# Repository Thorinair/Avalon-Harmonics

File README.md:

# Avalon Harmonics

This repository provides a collection of modular synthesizer modules designed by Thorinair under the brand name "Avalon Harmonics". The modules are all designed to have some associations with the [Avali](https://avali.fandom.com/wiki/The_Official_Avali_Wiki) fictional species and to have some unique functionalities - mostly stuff that I needed but couldn't readily find elsewhere.

* **Official Website:** [avalon-harmonics.com](https://avalon-harmonics.com/)
* **Official Twitter:** [@AvalonHarmonics](https://twitter.com/AvalonHarmonics)
* **Official Instagram:** [avalonharmonics](https://www.instagram.com/avalonharmonics/)

## Licensing

All hardware designs are licensed under the [cc-by-sa-4.0](https://creativecommons.org/licenses/by-sa/4.0/legalcode) license.

If designing a derivative module based on one of Avalon Harmonics modules, do not use the name "Avalon Harmonics". Additionally, you should not call the derivative module as one of the original Avalon Harmonics modules.

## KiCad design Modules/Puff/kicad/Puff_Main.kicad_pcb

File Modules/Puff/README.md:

# Avalon Harmonics Puff

**Stereo multimode filter with Ping input**

Puff is a stereo multimode filter with a state variable circuit. The filter provides separate Low Pass, Band Pass and High Pass outputs for both channels, has an attenuvertable CV input, a V/OCT input, and a dedicated Ping input. The circuit has some interesting quirks in its design, resulting in some very gritty sounds in higher resonance levels. Note that the filter can't continuously self-oscillate. **Features a golden (ENIG coated) panel.**

The filter has two audio inputs for a left and right channel. For convenience, right channel is normalled to the left channel when nothing is plugged into it. Both left and right channels have separate LP, BP and HP outputs, allowing all three of the filter types to be used at the same time.

Filter circuit is based on Thomas Henry's VCF circuit, with some modifications and adjustments. Cutoff can be controlled with the CUT knob, and resonance with the RES knob. CUT knob's effective range is from around 9 o'clock to 3 o'clock, with the extra range being useful when combined with a CV signal for more aggressive cutoffs etc. Signal fed into the CV input jack can be attenuverted with the ATN knob, allowing for inverting of an envelope signal, an LFO, or whatever is plugged in. Cutoff can also be controlled with a 1V/OCT signal through the V/OCT jack. Frequency of the cutoff can be tuned, and the tuning trimmer is exposed on the front panel where the tuning fork icon is, just to the bottom-left of the CUT knob. A screwdriver can be used to adjust it.

Resonance on this filter is interesting, as it gets progressively more unstable in higher ranges. Above around 3 o'clock of the RES knob, standing wave-like peaks start appearing in certain frequencies of the cutoff, which correspond to the frequency of the signal fed into the filter. These peaks can get quite loud on high resonance levels, so this whole section of the knob is marked with a warning symbol. An IN GAIN knob is provided, which can be used to lower the input signal's level. A quieter input signal will result in quieter resonance peaks, allowing the peaks to be tamed to a managable level.

Lastly, the filter has a dedicated PING input jack. A gate, trigger, or even an LFO can be plugged into this jack to ping the filter. The circuit simply converts an incoming signal so that, above a certain threshold, it causes a short DC offset, effectively plucking the filter's resonance. Ping only really works in high resonance levels, so I suggest maxing out the RES knob for this application. One way to use it is to connect a V/OCT signal, as well as a gate signal of a sequencer, and directly play notes on the filter. LP, BP and HP outputs will all have a slightly different sound when being pinged, so there is a lot to explore! An LED next to the PING jack flashes on each ping.

**CALIBRATION:** V/OCT of the cutoff can be calibrated. All modules I build and ship come pre-calibrated, but there might be a slight difference depending on your power supply or some other factors like temperature. To calibrate Puff, set the RES knob to the max, keep the audio inputs unplugged, connect your keyboard or sequencer's V/OCT and GATE to Puff's V/OCT and PING, and start playing notes. I suggest using a proper tuner, some modules can do this, and there is also Korg's ST1K tuner. Calibration of Puff is very similar to any VCO, but you need to constantly send it gates or triggers to keep the tone going, as it can't continuously self-oscillate.

*How did the name "Puff" happen? I wanted a cute, silly and unique name. I played around in my head with multiple different ones like Fluff, Floof, Poof, Puff, but eventually ended up with Puff. Puff as in, a pufferfish, a puffed up bird, etc!*

Visit Website: https://avalon-harmonics.com/module/Puff/

### Features

* Stereo multimode filter
* Separate LP, BP and HP outputs
* Attenuvertable CV input
* Tunable V/OCT input
* Dedicated Ping input
* Fully analog circuitry
* Wrong polarity protection
* Skiff friendly
* Size: 8HP
* Depth: 25mm
* Power: +12V: 35mA, -12V: 35mA

### Credits

* Filter circuit based on [Thomas Henry's VCF circuit](https://www.birthofasynth.com/Thomas_Henry/Pages/VCF-1.html)
* Tuning Fork Icon created by [Freepik - Flaticon](https://www.flaticon.com/free-icons/vibration)
* Alert Icon created by [Freepik - Flaticon](https://www.flaticon.com/free-icons/alert)

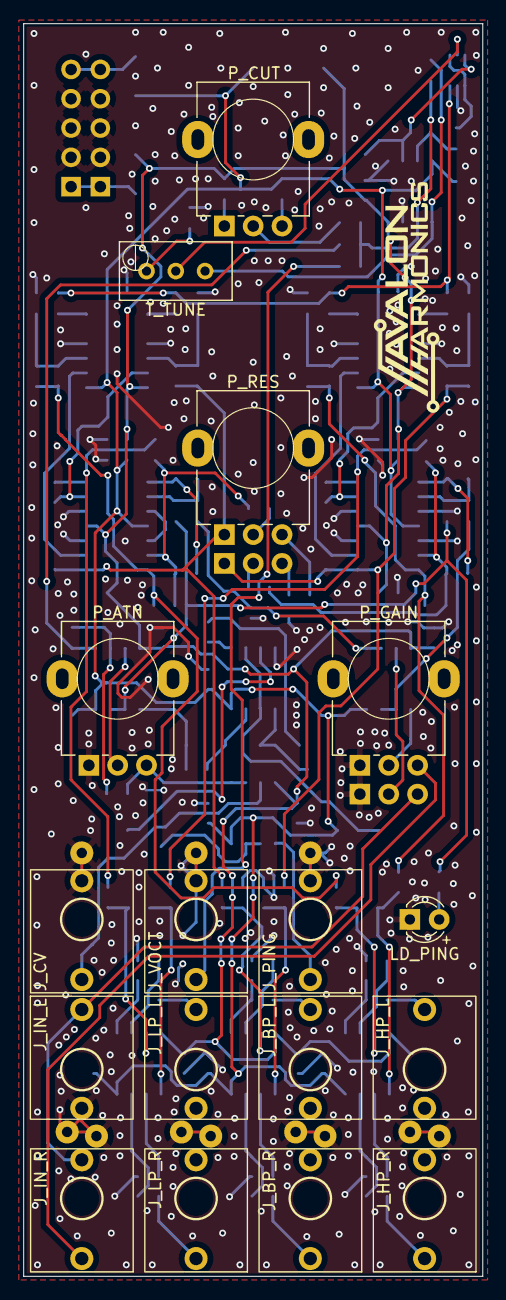
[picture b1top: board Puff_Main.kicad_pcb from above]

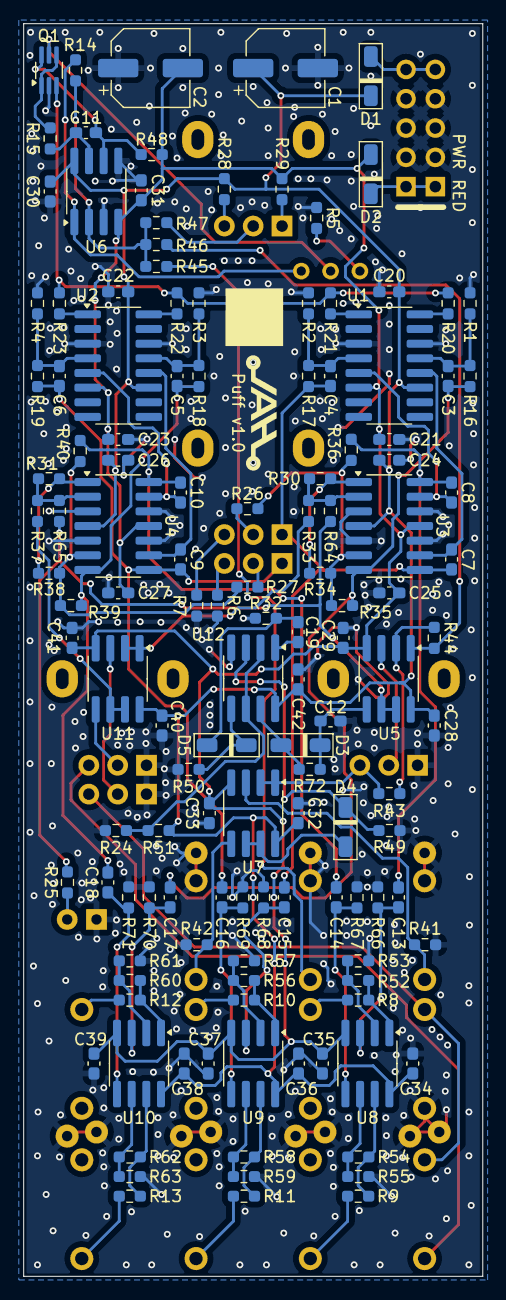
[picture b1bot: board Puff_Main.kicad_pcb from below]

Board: 2 copper layers, 39.8 x 108.6 mm, 150 parts (133 on the bottom side), 91 nets.

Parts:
C1, C2: 47uF; CP_Elec_6.3x5.3
C3, C4, C5, C6: 10pF; C_0603_1608Metric_Pad1.08x0.95mm_HandSolder
C7, C8, C9, C10: 330pF; C_0603_1608Metric_Pad1.08x0.95mm_HandSolder
C11: 1nF; C_0603_1608Metric_Pad1.08x0.95mm_HandSolder
C12: 47nF; C_0603_1608Metric_Pad1.08x0.95mm_HandSolder
C13, C14, C15, C16, C17, C18, C19, C20, C21, C22, C23, C24, C25, C26, C27, C28, C29, C30, C31, C32, C33, C34, C35, C36, C37, C38, C39, C40, C41, C42: 0.1uF; C_0603_1608Metric_Pad1.08x0.95mm_HandSolder
D1, D2: FM4001; D_SOD-123F_AH
D3, D4, D5: 1N4148W; D_SOD-123F_AH
J_BP_L: PJ301M-12; PJ301M-12 Offset
J_BP_R: PJ301M-12; PJ301M-12 Offset
J_CV: PJ301M-12
J_HP_L: PJ301M-12; PJ301M-12 Offset
J_HP_R: PJ301M-12; PJ301M-12 Offset
J_IN_L: PJ301M-12; PJ301M-12 Offset
J_IN_R: PJ301M-12; PJ301M-12 Offset
J_LP_L: PJ301M-12; PJ301M-12 Offset
J_LP_R: PJ301M-12; PJ301M-12 Offset
J_PING: PJ301M-12
J_VOCT: PJ301M-12
LD_PING: LED; LED_D3.0mm_FlatTop
PWR1: PWR_10_Pin; Eurorack Power 10 Pin
P_ATN: B50k; Potentiometer Alpha RD901F-40-00D
P_CUT: B100k; Potentiometer Alpha RD901F-40-00D
P_GAIN: A100k; Potentiometer Alpha Dual RD901F-40-00D
P_RES: B50k; Potentiometer Alpha Dual RD901F-40-00D
Q1: BCM857BS; SOT-363_SC-70-6_Handsoldering
R1, R2, R3, R4: 22; R_0603_1608Metric_Pad0.98x0.95mm_HandSolder
R5: 390; R_0603_1608Metric_Pad0.98x0.95mm_HandSolder
R6, R7: 220; R_0603_1608Metric_Pad0.98x0.95mm_HandSolder
R8, R9, R10, R11, R12, R13: 1k; R_0603_1608Metric_Pad0.98x0.95mm_HandSolder
R14: 2k; R_0603_1608Metric_Pad0.98x0.95mm_HandSolder
R15: 5.6k; R_0603_1608Metric_Pad0.98x0.95mm_HandSolder
R16, R17, R18, R19: 11k; R_0603_1608Metric_Pad0.98x0.95mm_HandSolder
R20, R21, R22, R23, R28, R29: 15k; R_0603_1608Metric_Pad0.98x0.95mm_HandSolder
R24, R25: 22k; R_0603_1608Metric_Pad0.98x0.95mm_HandSolder
R26, R27: 27k; R_0603_1608Metric_Pad0.98x0.95mm_HandSolder
R30, R31, R32: 47k; R_0603_1608Metric_Pad0.98x0.95mm_HandSolder
R33, R34, R35, R36, R37, R38, R39, R40, R41, R42, R43, R44, R45, R46, R47, R48, R49, R50, R51, R52, R53, R54, R55, R56, R57, R58, R59, R60, R61, R62, R63: 100k; R_0603_1608Metric_Pad0.98x0.95mm_HandSolder
R64, R65: 200k; R_0603_1608Metric_Pad0.98x0.95mm_HandSolder
R66, R67, R68, R69, R70, R71: 240k; R_0603_1608Metric_Pad0.98x0.95mm_HandSolder
R72: 1M; R_0603_1608Metric_Pad0.98x0.95mm_HandSolder
T_TUNE: B100; Potentiometer_Bourns_3296W_Vertical
U1, U2: LM13700; SO-16_3.9x9.9mm_P1.27mm_AH
U3, U4: TL074; SO-14_3.9x8.65mm_P1.27mm_AH
U5, U6, U7, U8, U9, U10, U11, U12: TL072; SO-8_3.9x4.9mm_P1.27mm_AH

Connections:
+12V: C1.1, C20.1, C22.1, C24.1, C26.1, C28.1, C30.1, C32.1, C34.1, C36.1, C38.1, C40.1, C42.1, D1.1 (K), R28.2, R51.2, U1.11 (V+), U2.11 (V+), U3.4 (V+), U4.4 (V+), U5.8 (V+), U6.8 (V+), U7.8 (V+), U8.8 (V+), U9.8 (V+), U10.8 (V+), U11.8 (V+), U12.8 (V+)
-12V: C2.2, C21.2, C23.2, C25.2, C27.2, C29.2, C31.2, C33.2, C35.2, C37.2, C39.2, C41.2, D2.2 (A), R29.1, R48.1, U1.6 (V-), U2.6 (V-), U3.11 (V-), U4.11 (V-), U5.4 (V-), U6.4 (V-), U7.4 (V-), U8.4 (V-), U9.4 (V-), U10.4 (V-), U11.4 (V-)
/ATN: P_ATN.3, R43.2, U7.1, U7.2 (-)
/BP_L: C4.1, C7.2, C15.1, P_RES.1, R17.2, U3.8
/BP_R: C6.1, C9.2, C16.1, P_RES.4, R19.2, U4.8
/CTRL: Q1.3 (C2), R20.1, R21.1, R22.1, R23.1
/DIV: R24.1, R51.1, U12.2 (-), U12.6 (-)
/HP_L: C3.1, C17.1, R16.2, R35.1, U3.7
/HP_R: C5.1, C18.1, R18.2, R39.1, U4.7
/IN_L: R33.2, U11.1, U11.2 (-)
/IN_PING: D4.2 (A), U7.6 (-), U7.7
/IN_R: R37.2, U11.6 (-), U11.7
/LP_L: C8.2, C13.1, R36.1, U3.14
/LP_R: C10.2, C14.1, R40.1, U4.14
/PING: R25.2, R64.2, R65.2, U5.6 (-), U5.7
/RES_L_2: P_RES.2, R26.2
/RES_R_2: P_RES.5, R27.2
/VOCT: J_VOCT.SIG, R45.2
GND: C1.2, C2.1, C12.2, C20.2, C21.1, C22.2, C23.1, C24.2, C25.1, C26.2, C27.1, C28.2, C29.1, C30.2, C31.1, C32.2, C33.1, C34.2, C35.1, C36.2, C37.1, C38.2, C39.1, C40.2, C41.1, C42.2, J_BP_L.GND, J_BP_R.GND, J_CV.GND, J_CV.SW, J_HP_L.GND, J_HP_R.GND, J_IN_L.GND, J_IN_L.SW, J_IN_R.GND, J_LP_L.GND, J_LP_R.GND, J_PING.GND, J_PING.SW, J_VOCT.GND, J_VOCT.SW, LD_PING.1 (K), PWR1.2 (GND), P_ATN.1, P_GAIN.1, P_GAIN.4, Q1.2 (B1), R1.1, R2.1, R3.1, R4.1, R5.1, R6.1, R7.1, R24.2, R32.2, R41.1, R42.1, R49.1, R50.1, R53.1, R55.1, R57.1, R59.1, R61.1, R63.1, R66.1, R67.1, R68.1, R69.1, R70.1, R71.1, U1.3 (+), U1.14 (+), U2.3 (+), U2.14 (+), U3.3 (+), U3.5 (+), U3.10 (+), U3.12 (+), U4.3 (+), U4.5 (+), U4.10 (+), U4.12 (+), U6.3 (+), U6.5 (+), U12.4 (V-)
unnamed: C11.2, R15.1, U6.7
unnamed: C19.1, U12.1
unnamed: D1.2 (A), PWR1.1 (+12V)
unnamed: D2.1 (K), PWR1.3 (-12V)
unnamed: D3.2 (A), R72.2, U12.7
unnamed: C12.1, D3.1 (K), R72.1, U5.5 (+)
unnamed: D4.1 (K), R49.2, U12.3 (+)
unnamed: C19.2, D5.2 (A), R32.1
unnamed: D5.1 (K), R50.2, U12.5 (+)
unnamed: J_BP_L.SIG, R10.1
unnamed: J_BP_R.SIG, R11.1
unnamed: J_HP_L.SIG, R12.1
unnamed: J_HP_R.SIG, R13.1
unnamed: J_IN_L.SIG, J_IN_R.SW, P_GAIN.6
unnamed: J_IN_R.SIG, P_GAIN.3
unnamed: J_LP_L.SIG, R8.1
unnamed: J_LP_R.SIG, R9.1
unnamed: LD_PING.2 (A), R25.1
unnamed: P_CUT.1, R29.2
unnamed: P_CUT.2, R47.2
unnamed: P_CUT.3, R28.1
unnamed: P_RES.3, R7.2
unnamed: P_RES.6, R6.2
unnamed: C11.1, Q1.6 (C1), R48.2, U6.6 (-)
unnamed: Q1.1 (E1), Q1.4 (E2), R15.2
unnamed: Q1.5 (B2), T_TUNE.2
unnamed: R5.2, T_TUNE.1
unnamed: R10.2, R56.1, U9.1
unnamed: R11.2, R58.1, U9.7
unnamed: R12.2, R60.1, U10.1
unnamed: R13.2, R62.1, U10.7
unnamed: R14.1, T_TUNE.3, U6.1
unnamed: R20.2, U1.16
unnamed: R21.2, U1.1
unnamed: R22.2, U2.16
unnamed: R23.2, U2.1
unnamed: R30.1, R34.2, U3.1
unnamed: R31.1, R38.2, U4.1
unnamed: R44.1, R46.2, U5.1
unnamed: R8.2, R52.1, U8.1
unnamed: R9.2, R54.1, U8.7
unnamed: C3.2, R1.2, R16.1, U1.13 (-)
unnamed: C4.2, R2.2, R17.1, U1.4 (-)
unnamed: C5.2, R3.2, R18.1, U2.13 (-)
unnamed: C6.2, R4.2, R19.1, U2.4 (-)
unnamed: R30.2, R33.1, R64.1, U3.2 (-)
unnamed: R26.1, R34.1, R35.2, R36.2, U3.6 (-)
unnamed: C7.1, U1.12, U3.9 (-)
unnamed: C8.1, U1.5, U3.13 (-)
unnamed: R31.2, R37.1, R65.1, U4.2 (-)
unnamed: R27.1, R38.1, R39.2, R40.2, U4.6 (-)
unnamed: C9.1, U2.12, U4.9 (-)
unnamed: C10.1, U2.5, U4.13 (-)
unnamed: P_ATN.2, U5.3 (+)
unnamed: R43.1, R44.2, U5.2 (-)
unnamed: R14.2, R45.1, R46.1, R47.1, U6.2 (-)
unnamed: J_CV.SIG, R41.2, U7.3 (+)
unnamed: J_PING.SIG, R42.2, U7.5 (+)
unnamed: C13.2, R66.2, U8.3 (+)
unnamed: R52.2, R53.2, U8.2 (-)
unnamed: C14.2, R67.2, U8.5 (+)
unnamed: R54.2, R55.2, U8.6 (-)
unnamed: C15.2, R68.2, U9.3 (+)
unnamed: R56.2, R57.2, U9.2 (-)
unnamed: C16.2, R69.2, U9.5 (+)
unnamed: R58.2, R59.2, U9.6 (-)
unnamed: C17.2, R70.2, U10.3 (+)
unnamed: R60.2, R61.2, U10.2 (-)
unnamed: C18.2, R71.2, U10.5 (+)
unnamed: R62.2, R63.2, U10.6 (-)
unnamed: P_GAIN.5, U11.3 (+)
unnamed: P_GAIN.2, U11.5 (+)

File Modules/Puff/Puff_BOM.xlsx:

Avalon Harmonics Puff
Qty | Value | Package | Ref | Description | Link |  |  |  | Alt Link
8 | 22 | R-0603 | R1-R8 | Resistor SMD | https://www.tme.eu/de/en/details/smd0603-22r-1%25/smd-resist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
2 | 220 | R-0603 | R6, R7 | Resistor SMD | https://www.tme.eu/de/en/details/smd0603-220r-1%25/smd-resis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
1 | 390 | R-0603 | R5 | Resistor SMD | https://www.tme.eu/de/en/details/smd0603-390r-1%25/smd-resis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
6 | 1k | R-0603 | R8-R13 | Resistor SMD | https://www.tme.eu/de/en/details/smd0603-1k-1%25/smd-resisto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
1 | 2k | R-0603 | R14 | Resistor SMD | https://www.tme.eu/de/en/details/smd0603-2k-1%25/smd-resisto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
1 | 5.6k | R-0603 | R15 | Resistor SMD | https://www.tme.eu/de/en/details/smd0603-5k6-1%25/smd-resist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
4 | 11k | R-0603 | R16-R19 | Resistor SMD | https://www.tme.eu/de/en/details/smd0603-11k-1%25/smd-resist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
6 | 15k | R-0603 | R20-R23, R28, R29 | Resistor SMD | https://www.tme.eu/de/en/details/smd0603-15k-1%25/smd-resist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
2 | 22k | R-0603 | R24, R25 | Resistor SMD | https://www.tme.eu/de/en/details/smd0603-22k-1%25/smd-resist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
2 | 27k | R-0603 | R26, R27 | Resistor SMD | https://www.tme.eu/de/en/details/smd0603-27k-1%25/smd-resist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
3 | 47k | R-0603 | R30-R32 | Resistor SMD | https://www.tme.eu/de/en/details/smd0603-47k-1%25/smd-resist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
31 | 100k | R-0603 | R33-R63 | Resistor SMD | https://www.tme.eu/de/en/details/smd0603-100k-1%25/smd-resis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
2 | 200k | R-0603 | R64, R65 | Resistor SMD | https://www.tme.eu/de/en/details/smd0603-200k-1%25/smd-resis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
6 | 240k | R-0603 | R66-R71 | Resistor SMD | https://www.tme.eu/de/en/details/crcw0603240kfktabc/smd-resi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
1 | 1M | R-0603 | R72 | Resistor SMD | https://www.tme.eu/de/en/details/cq0603-1m-1%25/smd-resistor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
1 | B100 | 3296W | T_TUNE | Multiturn Trimmer THT | https://www.thonk.co.uk/shop/25-turn-trimmer-potentiometer/
4 | 10pF | C-0603 | C3-C6 | Ceramic Capacitor SMD | https://www.tme.eu/de/en/details/0603n100k500ct/mlcc-smd-cap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
4 | 330pF | C-0603 | C7-C10 | Ceramic Capacitor SMD | https://www.tme.eu/de/en/details/0603b331k500ct/mlcc-smd-cap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
1 | 1nF | C-0603 | C11 | Ceramic Capacitor SMD | https://www.tme.eu/de/en/details/cl10b102kb8wpnc/mlcc-smd-ca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
1 | 47nF | C-0603 | C12 | Ceramic Capacitor SMD | https://www.tme.eu/de/en/details/cl10b473kb8nnnc/mlcc-smd-ca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
30 | 0.1uF | C-0603 | C13-C42 | Ceramic Capacitor SMD | https://www.tme.eu/de/en/details/0603b104k500ct/mlcc-smd-cap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
2 | 47uF | E-6.3x5.3mm | C1, C2 | Electrolytic Capacitor SMD | https://www.tme.eu/de/en/details/sc1e476m6l005vr/smd-electro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
2 | FM4001 | SOD123F | D1, D2 | Rectifier Diode SMD | https://www.tme.eu/de/en/details/fm4001-lge/smd-universal-di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
3 | 1N4148W | SOD123F | D3-D5 | Switching Diode SMD | https://www.tme.eu/de/en/details/1n4148w-dio/smd-universal-d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
1 | BCM857BS | SOT-363 | Q1 | PNP Dual Package SMD | https://www.tme.eu/de/en/details/bcm857bs.115/pnp-smd-transi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
2 | LM13700 | SO16 | U1, U2 | Dual OTA SMD | https://www.tme.eu/de/en/details/lm13700mx_nopb/smd-operatio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
2 | TL074 | SO14 | U3, U4 | Quad Op Amp SMD | https://www.tme.eu/de/en/details/tl074bcdt/smd-operational-a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
8 | TL072 | SO8 | U5-U12 | Dual Op Amp SMD | https://www.tme.eu/de/en/details/tl072cdr/smd-operational-am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
1 | B50k | Pot 9mm Alpha D-Shaft CENTRE DETENT* | P_ATN | Potentiometer Metal | https://www.thonk.co.uk/shop/alpha-9mm-pots-dshaft/
1 | A100k | Pot 9mm Alpha D-Shaft DUAL GANG* | P_GAIN | Potentiometer Metal | https://www.thonk.co.uk/shop/alpha-d-shaft-dual-gang/
1 | B50k | Pot 9mm Alpha D-Shaft DUAL GANG | P_RES | Potentiometer Metal | https://www.thonk.co.uk/shop/alpha-d-shaft-dual-gang/
1 | B100k | Pot 9mm Alpha D-Shaft | P_CUT | Potentiometer Metal | https://www.thonk.co.uk/shop/alpha-9mm-pots-dshaft/
1 | OSO5PA3HE4B | LED 3mm Flat | LD_PING | LED Orange | https://www.tme.eu/de/en/details/oso5pa3he4b/tht-leds-3mm/op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
11 | Thonkiconn | PJ398SM | J_CV, J_VOCT, J_PING, J_IN_L, J_IN_R, J_LP_L, J_LP_R, J_BP_L, J_BP_R, J_HP_L, J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 | Audio Jack | https://www.thonk.co.uk/shop/thonkiconn/
1 | 2x5 | Male Header 2.54mm | PWR | Header Connector | https://www.tme.eu/de/en/details/zl202-10g/pin-headers/connf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
4 | Black | Pushernut |  | Jack Nut | https://pushermanproductions.com/products/pushernuts-round-m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
6 | Gold | Pushernut |  | Jack Nut | https://pushermanproductions.com/products/pushernuts-round-m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
1 | Red | Pushernut |  | Jack Nut | https://pushermanproductions.com/products/pushernuts-round-m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
4 | Black | Alpha 9mm Nut |  | Potentiometer Nut | https://www.thonk.co.uk/shop/black-nuts-washers/
2 | Black D-Shaft Line | Bastl Style Alu Knob 10mm |  | Potentiometer Knob | https://www.thonk.co.uk/shop/bastl-knobs/
2 | Black D-Shaft Line | Bastl Style Alu Knob 15mm |  | Potentiometer Knob | https://www.thonk.co.uk/shop/bastl-knobs/
 | Parts with underline are on the front side of the PCB!
 | * Do not use the included washer. Tighten very gently so the PCB doesn't get sc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

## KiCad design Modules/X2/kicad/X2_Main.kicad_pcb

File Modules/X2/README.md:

# Avalon Harmonics X2

**4 channel voltage doubler**

X2 is a simple and compact module which will double the voltage level of any signal. Designed to be a perfect companion for the Avalon Harmonics CVMod8 V2 and CVMod4. **Features a golden (ENIG coated) panel.**

Some modules expect a higher voltage than 5V to trigger. This is where this module comes to bridge the gap. The module provides 4 independent channels, each providing exactly 2x gain of the input voltage. This functionality allows it to expand the voltage range of CVMod8 V2, CVMod4 or any other module that outputs up to around 5V.

Using special rail-to-rail operational amplifiers, the module can reach up to 10V on the output, provided the main rack power supply is within specs. A range of +5V to -5V will become +10V to -10V.

NOTE: New version of the module has the power connector fitting issue resolved by offsetting all jack holes on the front panel up by 1mm.

Visit Website: https://avalon-harmonics.com/module/X2/

### Features

* Slim 2 HP design
* 4 independent channels
* Provides exactly 2x gain for each signal
* Wrong polarity protection
* Skiff friendly
* Size: 2HP
* Depth: 25mm
* Power: +12V: 5mA, -12V: 5mA

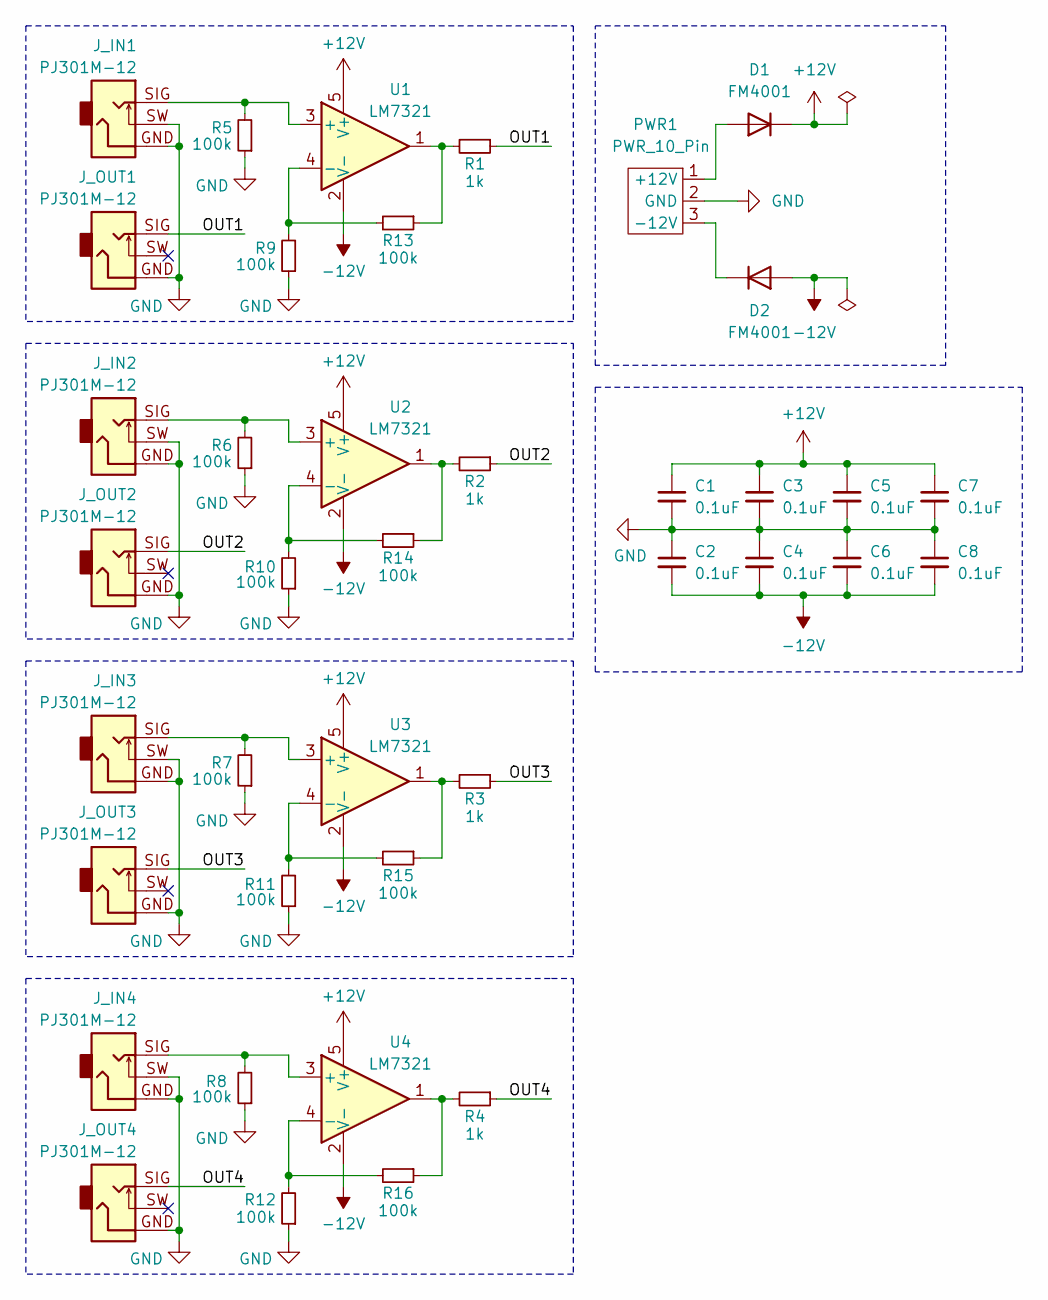
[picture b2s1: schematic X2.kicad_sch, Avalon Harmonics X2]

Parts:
C1, C2, C3, C4, C5, C6, C7, C8: 0.1uF; C_0603_1608Metric_Pad1.08x0.95mm_HandSolder
D1, D2: FM4001; D_SOD-123F_AH
J_IN1, J_IN2, J_IN3, J_IN4: PJ301M-12; PJ301M-12 Offset
J_OUT1, J_OUT2, J_OUT3, J_OUT4: PJ301M-12; PJ301M-12 Offset
PWR1: PWR_10_Pin; Eurorack Power 10 Pin
R1, R2, R3, R4: 1k; R_0603_1608Metric_Pad0.98x0.95mm_HandSolder
R5, R6, R7, R8, R9, R10, R11, R12, R13, R14, R15, R16: 100k; R_0603_1608Metric_Pad0.98x0.95mm_HandSolder
U1, U2, U3, U4: LM7321; SOT-23-5_HandSoldering

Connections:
+12V: C1.1, C3.1, C5.1, C7.1, D1.1 (K), U1.5 (V+), U2.5 (V+), U3.5 (V+), U4.5 (V+)
-12V: C2.2, C4.2, C6.2, C8.2, D2.2 (A), U1.2 (V-), U2.2 (V-), U3.2 (V-), U4.2 (V-)
/OUT1: J_OUT1.SIG, R1.1
/OUT2: J_OUT2.SIG, R2.1
/OUT3: J_OUT3.SIG, R3.1
/OUT4: J_OUT4.SIG, R4.1
GND: C1.2, C2.1, C3.2, C4.1, C5.2, C6.1, C7.2, C8.1, J_IN1.GND, J_IN1.SW, J_IN2.GND, J_IN2.SW, J_IN3.GND, J_IN3.SW, J_IN4.GND, J_IN4.SW, J_OUT1.GND, J_OUT2.GND, J_OUT3.GND, J_OUT4.GND, PWR1.2 (GND), R5.1, R6.1, R7.1, R8.1, R9.1, R10.1, R11.1, R12.1
unnamed: D1.2 (A), PWR1.1 (+12V)
unnamed: D2.1 (K), PWR1.3 (-12V)
unnamed: R1.2, R13.1, U1.1
unnamed: R2.2, R14.1, U2.1
unnamed: R3.2, R15.1, U3.1
unnamed: R4.2, R16.1, U4.1
unnamed: J_IN1.SIG, R5.2, U1.3 (+)
unnamed: R9.2, R13.2, U1.4 (-)
unnamed: J_IN2.SIG, R6.2, U2.3 (+)
unnamed: R10.2, R14.2, U2.4 (-)
unnamed: J_IN3.SIG, R7.2, U3.3 (+)
unnamed: R11.2, R15.2, U3.4 (-)
unnamed: J_IN4.SIG, R8.2, U4.3 (+)
unnamed: R12.2, R16.2, U4.4 (-)

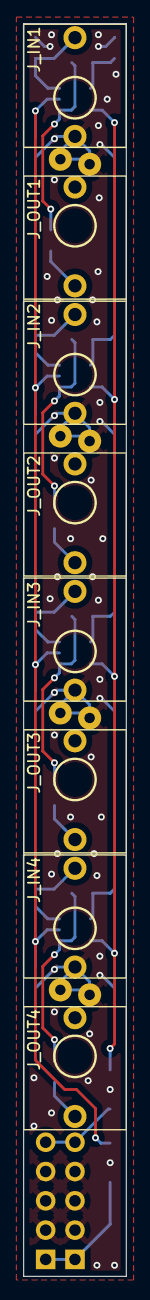
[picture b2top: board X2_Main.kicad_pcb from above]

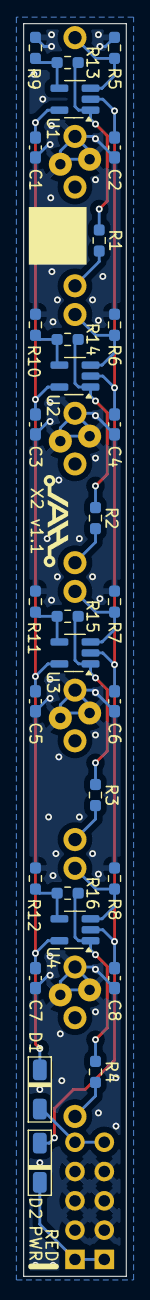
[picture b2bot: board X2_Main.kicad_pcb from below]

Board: 2 copper layers, 8.9 x 108.6 mm, 39 parts (31 on the bottom side), 21 nets.

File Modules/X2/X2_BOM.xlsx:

Avalon Harmonics X2
Qty | Value | Package | Ref | Description | Link |  |  |  | Alt Link
4 | 1k | R-0603 | R1-R4 | Resistor SMD | https://www.tme.eu/de/en/details/smd0603-1k-1%25/smd-resisto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
12 | 100k | R-0603 | R5-R16 | Resistor SMD | https://www.tme.eu/de/en/details/smd0603-100k-1%25/smd-resis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
8 | 0.1uF | C-0603 | C1-C8 | Ceramic Capacitor SMD | https://www.tme.eu/de/en/details/0603b104k500ct/mlcc-smd-cap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
2 | FM4001 | SOD123F | D1, D2 | Rectifier Diode SMD | https://www.tme.eu/de/en/details/fm4001-lge/smd-universal-di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
4 | LM7321 | SOT23-5 | U1-U4 | Single Rail-To-Rail Op Amp SMD | https://www.tme.eu/de/en/details/lm7321mfx_nopb/smd-operatio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
8 | Thonkiconn | PJ398SM | J_IN1-J_IN4, J_OUT1-J_OUT4 | Audio Jack | https://www.thonk.co.uk/shop/thonkiconn/
1 | 2x5 | Male Header 2.54mm | PWR | Header Connector | https://www.tme.eu/de/en/details/zl202-10g/pin-headers/connf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
4 | Black | Pushernut |  | Jack Nut | https://pushermanproductions.com/products/pushernuts-round-m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
4 | Gold | Pushernut |  | Jack Nut | https://pushermanproductions.com/products/pushernuts-round-m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
 | Parts with underline are on the front side of the PCB!

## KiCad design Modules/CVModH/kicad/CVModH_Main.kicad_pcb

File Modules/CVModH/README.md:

# Avalon Harmonics CVModH

**2 channel CV attenuverter, offset and mixer in 1U format**

CVModH is functionally identical to the Avalon Harmonics CVMod4 and CVMod8 V2, but provides 2 channels and is designed to be used in a 1U row. The whole layout has been adjusted to make it horizontal, while preserving what makes other CVMod modules useful. This module is a perfect match with the Avalon Harmonics MiniDJ, expanding the original knobs to sliders instead. **Features a golden (ENIG coated) panel.**

The module provides 2 channels of independent CV attenuverters and offset controls, as well as offset polarity switches and a forward switch for mixing the channels together.

Each channel can be used as a static voltage source with the output available on the right-most column of jacks. Sliders control the voltage, and the voltage can be bipolar (+5V to -5V) or unipolar (+5V to 0V) by flipping the corresponding switch on the bottom. Behavior is bipolar when switched to the top and unipolar when switched to the bottom. Internally, voltage regulators ensure a precise voltage source. Note that there is a 5V spike when switching the polarity.

Each channel also has a signal input (left column of jacks) with a corresponding attenuverter knob to the left. The knobs have a centre detent as this is where the input gain is set to 0. When turned clockwise, level of the signal can be adjusted up to unity gain. When turned counter-clockwise, signal gets inverted up to a negative unity gain. The input signal is mixed together with the previously mentioned slider value, allowing the sliders to offset the incoming signal.

Output of first channel can be forwarded to the second channel by flipping the middle switch to the bottom. The signal is then mixed together with the attenuverted CV and offset of the second channel. Each channel has the following formula:

`output = input * attenuverter + offset + output_prev`

* `input` is whatever signal is plugged into the left column jack.
* `attenuverter` is the position of the attenuverter knob and can range from -1 to 1.
* `offset` is the offset voltage set by the slider and polarity switch. Can range from +5V to -5V or 5V to 0V.
* `output_prev` is the output signal from the previous channel, if the forwarding switch has been flipped.

The forwarding feature can be used to combine the two channels together acting as a CV mixer with outputs still available on each channel. Plugging a cable into one of the outputs does not interrupt the forwarding, so it is possible to make use of submixes. If a need arises for an audio mixer, setting offsets to unipolar mode and sliding them all the way down will achieve this kind of behavior.

Lastly, a bipolar LED exists for each channel as a clear indicator of the status of the output voltage.

Visit Website: https://avalon-harmonics.com/module/CVModH/

### Features

* 2 independent channels
* Offset for both channels with a polarity switch
* Both channels with an input and attenuverter
* Togglable forwarding of output to second channel
* Status LEDs for both channels
* Wrong polarity protection
* Skiff friendly
* Size: 22HP 1U
* Depth: 25mm
* Power: +12V: 28mA, -12V: 25mA

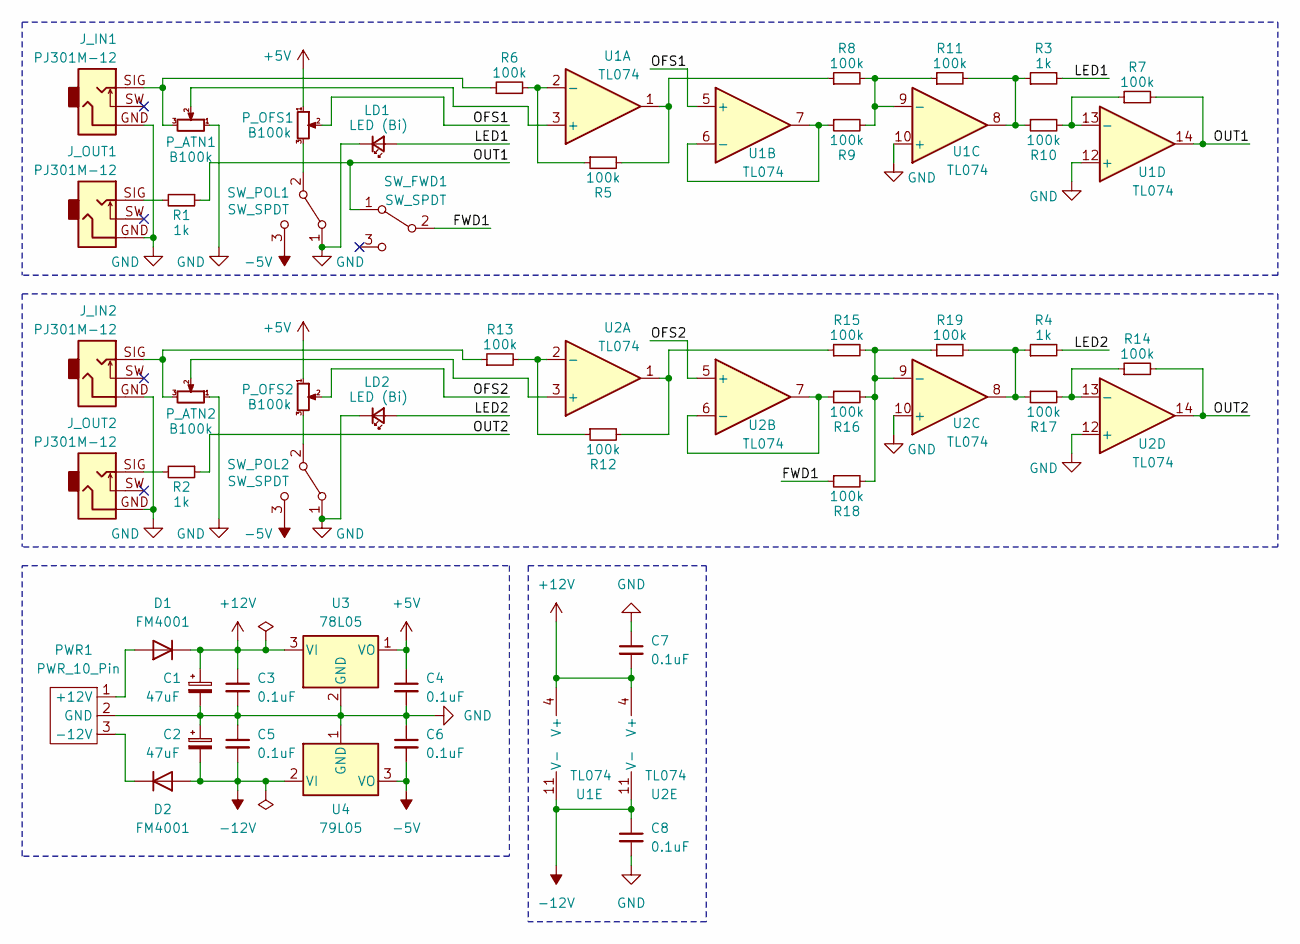
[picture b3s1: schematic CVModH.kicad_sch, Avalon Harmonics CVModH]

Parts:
C1, C2: 47uF; CP_Elec_6.3x5.3
C3, C4, C5, C6, C7, C8: 0.1uF; C_0603_1608Metric_Pad1.08x0.95mm_HandSolder
D1, D2: FM4001; D_SOD-123F_AH
J_IN1, J_IN2: PJ301M-12; PJ301M-12 Offset
J_OUT1, J_OUT2: PJ301M-12; PJ301M-12 Offset
LD1, LD2: LED (Bi); LED_D3.0mm_FlatTop
PWR1: PWR_10_Pin; Eurorack Power 10 Pin
P_ATN1: B100k; Potentiometer Song Huei 9mm Trimmer CutA
P_ATN2: B100k; Potentiometer Song Huei 9mm Trimmer CutB
P_OFS1: B100k; Potentiometer_Bourns_PTA3043_Single_Slide_CutB
P_OFS2: B100k; Potentiometer_Bourns_PTA3043_Single_Slide_CutA
R1, R2, R3, R4: 1k; R_0603_1608Metric_Pad0.98x0.95mm_HandSolder
R5, R6, R7, R8, R9, R10, R11, R12, R13, R14, R15, R16, R17, R18, R19: 100k; R_0603_1608Metric_Pad0.98x0.95mm_HandSolder
SW_FWD1: SW_SPDT; SPDT
SW_POL1, SW_POL2: SW_SPDT; SPDT
U1, U2: TL074; SO-14_3.9x8.65mm_P1.27mm_AH
U3: 78L05; SOT-89-3_Handsoldering
U4: 79L05; SOT-89-3_Handsoldering

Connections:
+5V: C4.1, P_OFS1.1, P_OFS2.1, U3.1 (VO)
+12V: C1.1, C3.1, C7.2, D1.1 (K), U1.4 (V+), U2.4 (V+), U3.3 (VI)
-5V: C6.2, SW_POL1.3 (C), SW_POL2.3 (C), U4.3 (VO)
-12V: C2.2, C5.2, C8.1, D2.2 (A), U1.11 (V-), U2.11 (V-), U4.2 (VI)
/FWD1: R18.1, SW_FWD1.2 (B)
/LED1: LD1.2 (A), R3.2
/LED2: LD2.2 (A), R4.2
/OFS1: P_OFS1.2, U1.5 (+)
/OFS2: P_OFS2.2, U2.5 (+)
/OUT1: R1.1, R7.2, SW_FWD1.1 (A), U1.14
/OUT2: R2.1, R14.2, U2.14
GND: C1.2, C2.1, C3.2, C4.2, C5.1, C6.1, C7.1, C8.2, J_IN1.GND, J_IN2.GND, J_OUT1.GND, J_OUT2.GND, LD1.1 (K), LD2.1 (K), PWR1.2 (GND), P_ATN1.1, P_ATN2.1, SW_POL1.1 (A), SW_POL2.1 (A), U1.10 (+), U1.12 (+), U2.10 (+), U2.12 (+), U3.2 (GND), U4.1 (GND)
unnamed: D1.2 (A), PWR1.1 (+12V)
unnamed: D2.1 (K), PWR1.3 (-12V)
unnamed: J_IN1.SIG, P_ATN1.3, R6.1
unnamed: J_IN2.SIG, P_ATN2.3, R13.1
unnamed: J_OUT1.SIG, R1.2
unnamed: J_OUT2.SIG, R2.2
unnamed: R5.2, R8.1, U1.1
unnamed: R3.1, R10.1, R11.2, U1.8
unnamed: R12.2, R15.1, U2.1
unnamed: R4.1, R17.1, R19.2, U2.8
unnamed: P_OFS1.3, SW_POL1.2 (B)
unnamed: P_OFS2.3, SW_POL2.2 (B)
unnamed: P_ATN1.2, U1.3 (+)
unnamed: R5.1, R6.2, U1.2 (-)
unnamed: R9.1, U1.6 (-), U1.7
unnamed: R8.2, R9.2, R11.1, U1.9 (-)
unnamed: R7.1, R10.2, U1.13 (-)
unnamed: P_ATN2.2, U2.3 (+)
unnamed: R12.1, R13.2, U2.2 (-)
unnamed: R16.1, U2.6 (-), U2.7
unnamed: R15.2, R16.2, R18.2, R19.1, U2.9 (-)
unnamed: R14.1, R17.2, U2.13 (-)

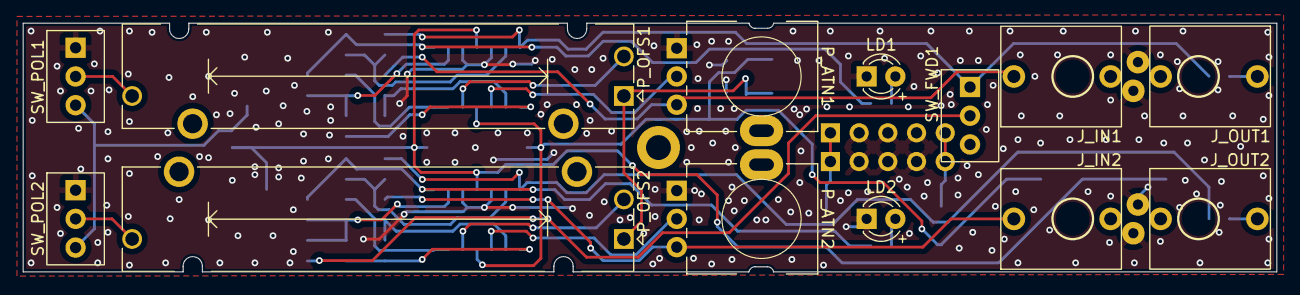
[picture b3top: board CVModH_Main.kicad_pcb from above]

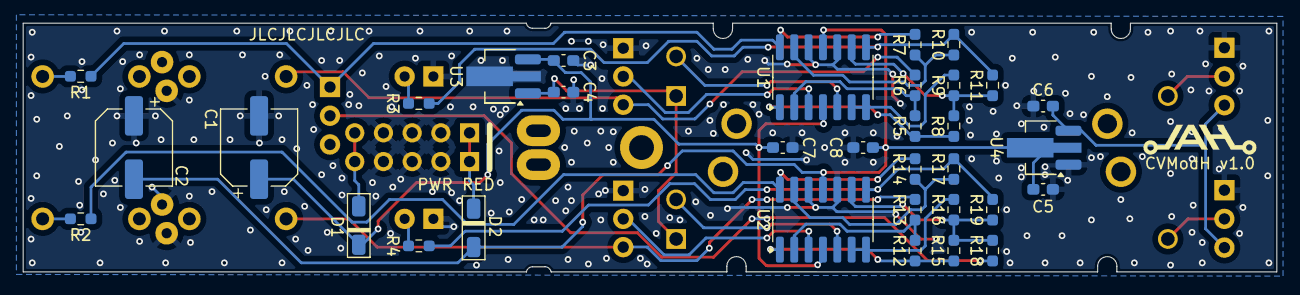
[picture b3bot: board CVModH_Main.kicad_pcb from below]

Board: 2 copper layers, 110.9 x 22.0 mm, 47 parts (34 on the bottom side), 34 nets.

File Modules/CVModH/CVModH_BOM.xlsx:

Avalon Harmonics CVModH
Qty | Value | Package | Ref | Description | Link |  |  |  | Alt Link
4 | 1k | R-0603 | R1-R4 | Resistor SMD | https://www.tme.eu/de/en/details/smd0603-1k-1%25/smd-resisto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
15 | 100k | R-0603 | R5-R19 | Resistor SMD | https://www.tme.eu/de/en/details/smd0603-100k-1%25/smd-resis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
6 | 0.1uF | C-0603 | C3-C8 | Ceramic Capacitor SMD | https://www.tme.eu/de/en/details/0603b104k500ct/mlcc-smd-cap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
2 | 47uF | E-6.3x5.3mm | C1, C2 | Electrolytic Capacitor SMD | https://www.tme.eu/de/en/details/sc1e476m6l005vr/smd-electro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
2 | FM4001 | SOD123F | D1, D2 | Rectifier Diode SMD | https://www.tme.eu/de/en/details/fm4001-lge/smd-universal-di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
2 | TL074 | SO14 | U1, U2 | Quad Op Amp SMD | https://www.tme.eu/de/en/details/tl074bcdt/smd-operational-a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
1 | 78L05 | SOT89 | U3 | Voltage Regulator 5V SMD | https://www.tme.eu/de/en/details/l78l05abutr/fixed-voltage-r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
1 | 79L05 | SOT89 | U4 | Voltage Regulator -5V NEGATIVE SMD | https://www.tme.eu/de/en/details/lm79l05a-cdi/fixed-voltage-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
2 | B100k | Pot 9mm Tall Trimmer CENTRE DETENT | P_ATN1, P_ATN2 | Potentiometer Plastic | https://www.thonk.co.uk/shop/ttpots/
2 | B100k PTA3043 -2015DPB104 | Bourns Slide Pot 30mm, 15mm L* | P_OFS1, P_OFS2 | Slide Potentiometer | https://www.mouser.de/ProductDetail/Bourns/PTA3043-2015DPB10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
2 | L-937EGW | LED 3mm Dome Bicolor | LD1, LD2 | LED Red/Green | https://www.tme.eu/de/en/details/l-937egw/tht-leds-3mm/kingb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
2 | SPDT ON-ON | Sub-Mini SPDT LOW PROFILE** | SW_POL1, SW_POL2 | Switch | https://www.thonk.co.uk/shop/sub-mini-toggle-switches/
1 | SPDT ON-ON | Sub-Mini SPDT*** | SW_FWD1 | Switch | https://www.thonk.co.uk/shop/sub-mini-toggle-switches/
4 | Thonkiconn | PJ398SM | J_IN1, J_IN2, J_OUT1, J_OUT2 | Audio Jack | https://www.thonk.co.uk/shop/thonkiconn/
1 | 2x5 | Male Header 2.54mm**** | PWR | Header Connector | https://www.tme.eu/de/en/details/zl202-80g/pin-headers/connf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
1 | M2*5 | M2 Screw |  | Screw | https://www.aliexpress.com/item/32810872544.html
1 | M2 | M2 Nut |  | Nut | https://www.aliexpress.com/item/1005002177898963.html
1 | M2, 10mm | M2 Standoff***** |  | Standoff | https://www.tme.eu/de/en/details/tfm-m2x10_dr211of/metal-spa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
2 | Black | Pushernut |  | Jack Nut | https://pushermanproductions.com/product/black-smooth-edge-j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
2 | Gold | Pushernut |  | Jack Nut | https://pushermanproductions.com/product/pushernuts-gold-smo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
2 | Black | Thonk Trimmer Topper |  | Trimmer Knob | https://www.thonk.co.uk/shop/tall-trimmer-toppers/
2 | Black | Sifam Sleek Slider Cap****** |  | Slider Knob | https://www.thonk.co.uk/shop/sifam-sleek-slider-caps/
 | Parts with underline are on the front side of the PCB!
 | * Slider pots should be soldered in before mounting the panel. Ensure they are 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
 | ** Use the included extra nut as a washer between the switches and the panel fo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
 | *** For SW_FWD1 switch, don't use the nut between the panel and the switch. Thi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
 | **** Snip off the pins below the switch almost flush to the PCB, otherwise you 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
 | ***** 10mm standoff is used between the panel and main PCB. Orient it so that t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
 | ****** Don't push the caps all the way down, otherwise they will slightly scrap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
